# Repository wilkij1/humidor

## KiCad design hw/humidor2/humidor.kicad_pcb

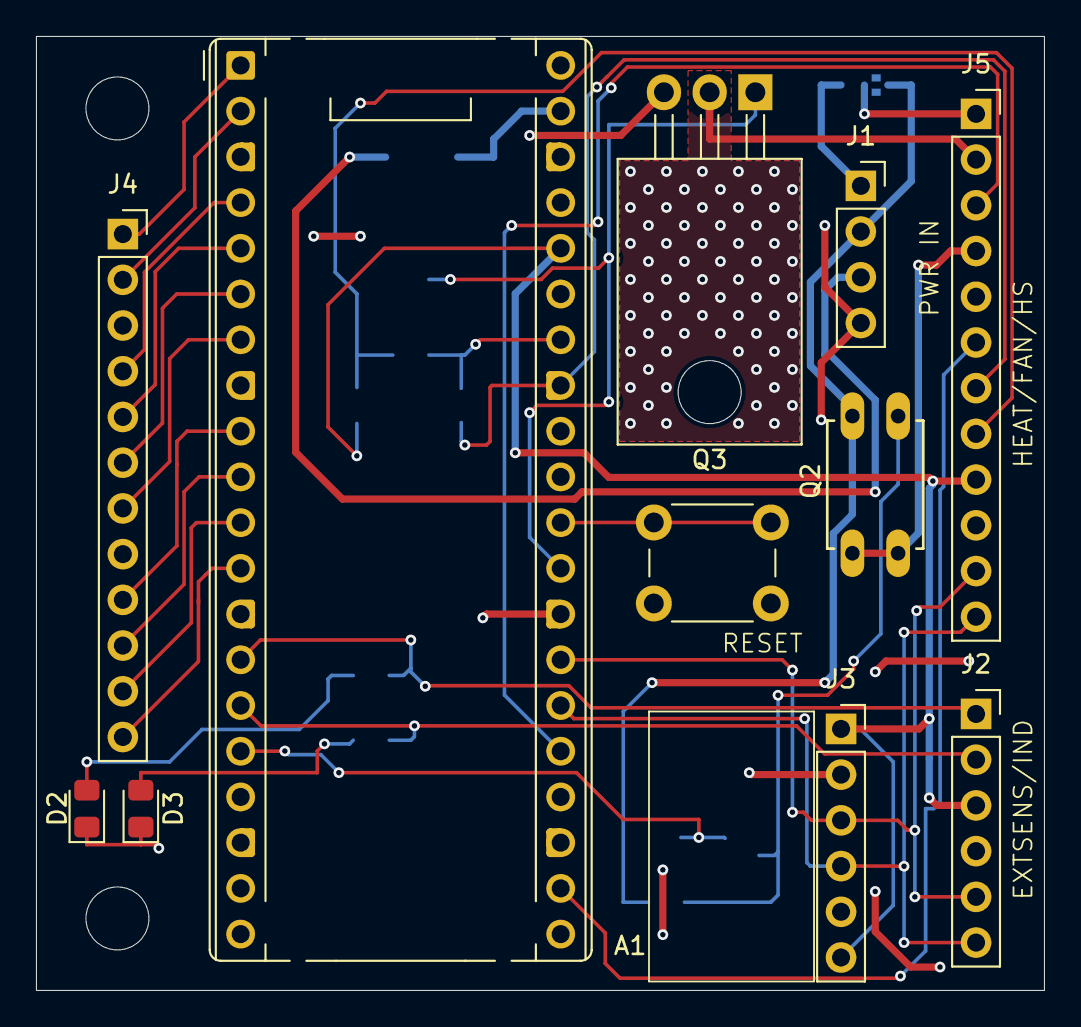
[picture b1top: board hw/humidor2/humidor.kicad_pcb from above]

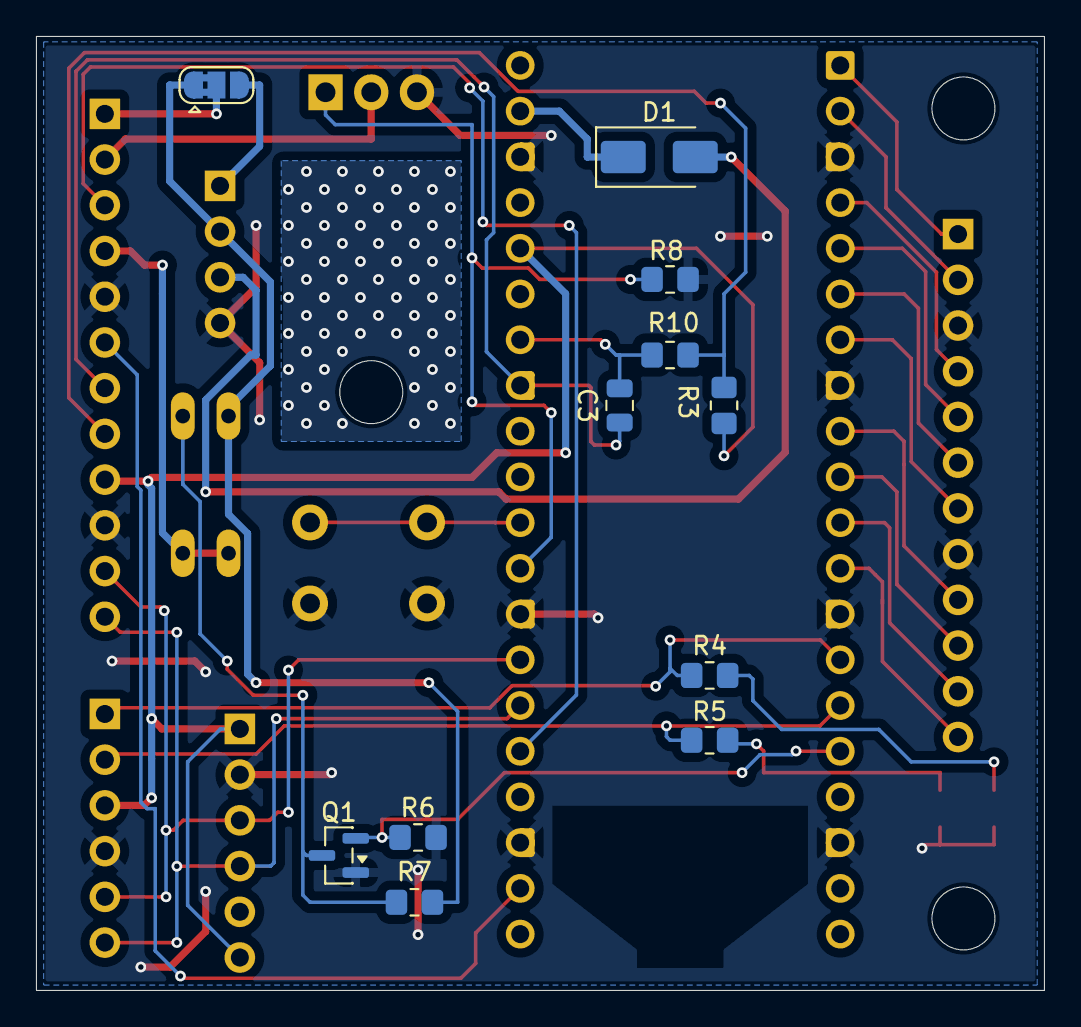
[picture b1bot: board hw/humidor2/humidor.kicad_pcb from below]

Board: 2 copper layers, 56.0 x 53.0 mm, 24 parts (11 on the bottom side), 34 nets.

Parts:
A1: RaspberryPi_Pico_W; RaspberryPi_Pico_Common_THT
C3: 100n; C_0805_2012Metric
D1: 1N5711; D_SMA
D2: RED LED; LED_0805_2012Metric_Pad1.15x1.40mm_HandSolder
D3: GRN LED; LED_0805_2012Metric_Pad1.15x1.40mm_HandSolder
H3, H4: MountingHole; MountingHole_3.5mm
J1: PWR IN; PinSocket_1x04_P2.54mm_Vertical
J2: PWR IN/EXTSENS/IND; PinSocket_1x06_P2.54mm_Vertical
J3: IN_SENSOR; PinSocket_1x06_P2.54mm_Vertical
J4: Conn_01x12; PinSocket_1x12_P2.54mm_Vertical
J5: HEAT/FAN/HS; PinSocket_1x12_P2.54mm_Vertical
JP2: SolderJumper_3_Bridged12; SolderJumper-3_P1.3mm_Bridged2Bar12_RoundedPad1.0x1.5mm
Q1: 2N7002; SOT-23
Q2: IRFD9120; C370-01
Q3: IRF540N; TO-220-3_Horizontal_TabDown
R3: 1k; R_0805_2012Metric_Pad1.20x1.40mm_HandSolder
R4, R5: 330; R_0805_2012Metric_Pad1.20x1.40mm_HandSolder
R6, R7, R8: 100k; R_0805_2012Metric_Pad1.20x1.40mm_HandSolder
R10: 1.6k; R_0805_2012Metric_Pad1.20x1.40mm_HandSolder
SW1: SW_Push; SW_PUSH_6mm_H5mm

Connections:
+3.3V: A1.36 (3V3), J2.3, J3.1, J3.6, J5.9, R3.1
+5V: D1.2 (A), J1.3
+12V: J1.2, JP2.1 (A), Q2.S, R7.1
/AGND: A1.33 (AGND), C3.2, J5.7
/AUX_HEAT: J1.1, JP2.3 (B)
/FAN_EN: A1.16 (GPIO12), Q1.2 (G), R6.1
/FAN_ON: A1.15 (GPIO11), J2.2, R5.1
/FAN_PWM: A1.22 (GPIO17), J5.6
/FAN_PWR: J5.4, Q2.D, Q2.D1
/HEAT_ON: A1.14 (GPIO10), J2.1, R4.1
/HEAT_PWM: A1.29 (GPIO22), Q3.1 (G), R8.1
/HEAT_PWR: J5.1, JP2.2 (C)
/HEAT_SW: J5.2, Q3.2 (D)
/SCL0: A1.27 (GPIO21), J2.5, J3.3, J5.11
/SDA0: A1.26 (GPIO20), J2.6, J3.4, J5.12
/TACH: A1.25 (GPIO19), J5.3
/T_HEATSINK: J5.8, R3.2, R10.2
GND: A1.3 (GND), A1.8 (GND), A1.13 (GND), A1.18 (GND), A1.23 (GND), A1.28 (GND), A1.38 (GND), D2.1 (K), D3.1 (K), J1.4, J2.4, J3.2, J4.3, J4.8, J5.5, J5.10, Q1.1 (S), Q3.3 (S), R6.2, R8.2, SW1.1
unnamed: A1.1 (GPIO0), J4.1
unnamed: A1.2 (GPIO1), J4.2
unnamed: A1.4 (GPIO2), J4.4
unnamed: A1.5 (GPIO3), J4.5
unnamed: A1.6 (GPIO4), J4.6
unnamed: A1.7 (GPIO5), J4.7
unnamed: A1.9 (GPIO6), J4.9
unnamed: A1.10 (GPIO7), J4.10
unnamed: A1.11 (GPIO8), J4.11
unnamed: A1.12 (GPIO9), J4.12
unnamed: A1.34 (GPIO28_ADC2), C3.1, R10.1
unnamed: A1.30 (RUN), SW1.2
unnamed: A1.39 (VSYS), D1.1 (K)
unnamed: D2.2 (A), R4.2
unnamed: D3.2 (A), R5.2
unnamed: Q1.3 (D), Q2.G, R7.2

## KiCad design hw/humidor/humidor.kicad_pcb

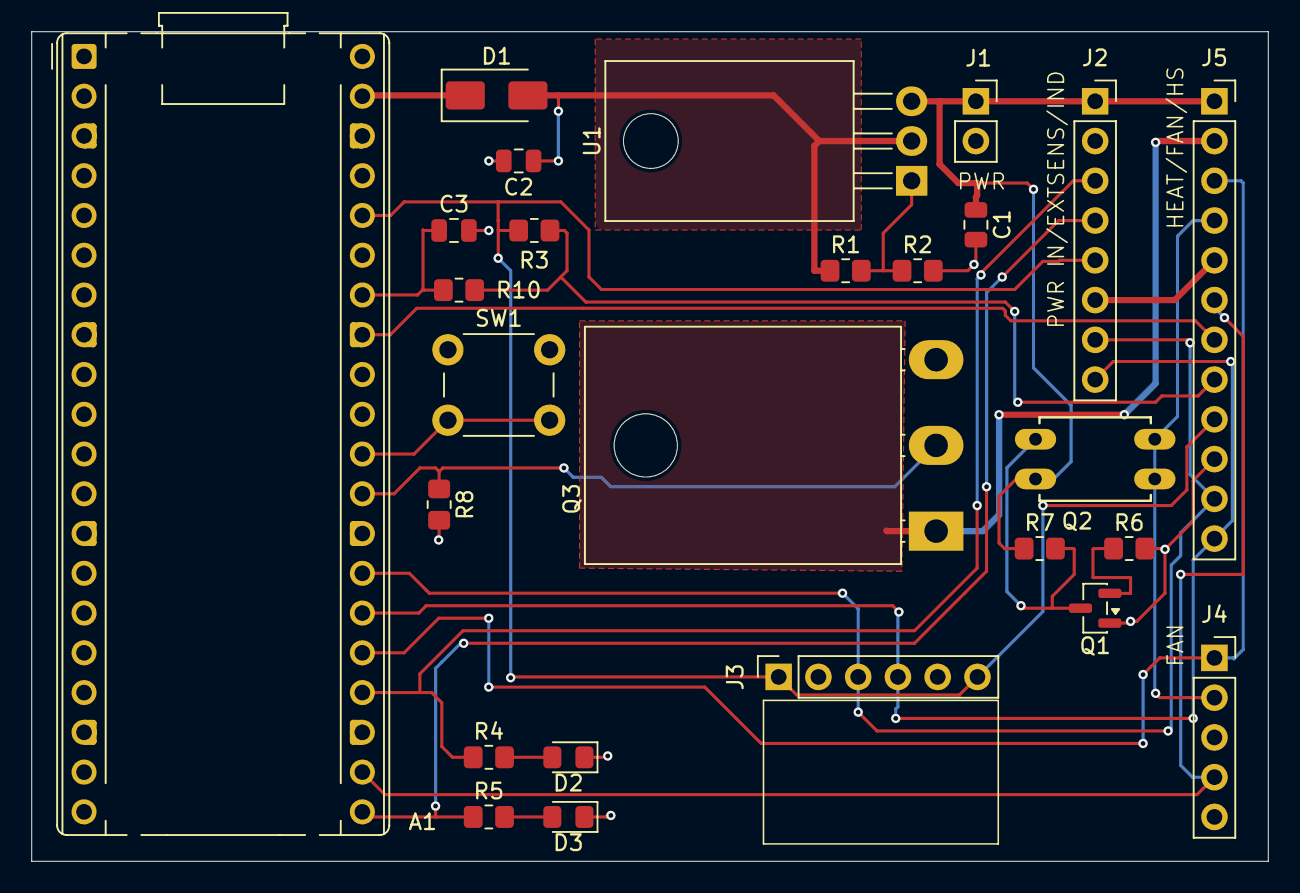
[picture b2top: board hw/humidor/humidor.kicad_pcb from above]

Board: 2 copper layers, 79.0 x 53.0 mm, 26 parts (0 on the bottom side), 23 nets.

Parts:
A1: RaspberryPi_Pico_W; RaspberryPi_Pico_Common_THT
C1, C2: 22u; C_0805_2012Metric
C3: 100n; C_0805_2012Metric
D1: 1N5711; D_SMA
D2: RED LED; LED_0805_2012Metric_Pad1.15x1.40mm_HandSolder
D3: GRN LED; LED_0805_2012Metric_Pad1.15x1.40mm_HandSolder
J1: PWR IN; PinSocket_1x02_P2.54mm_Vertical
J2: PWR IN/EXTSENS/IND; PinSocket_1x08_P2.54mm_Vertical
J3: IN_SENSOR; PinSocket_1x06_P2.54mm_Vertical
J4: Conn_01x05; PinSocket_1x05_P2.54mm_Vertical
J5: HEAT/FAN/HS; PinSocket_1x12_P2.54mm_Vertical
Q1: 2N7002; SOT-23
Q2: IRFD9120; C370-01
Q3: IRL540; TO-218-3_Horizontal_TabDown
R1: 110; R_0805_2012Metric_Pad1.20x1.40mm_HandSolder
R2: 360; R_0805_2012Metric_Pad1.20x1.40mm_HandSolder
R3: 1k; R_0805_2012Metric_Pad1.20x1.40mm_HandSolder
R4, R5: 330; R_0805_2012Metric_Pad1.20x1.40mm_HandSolder
R6, R7, R8: 100k; R_0805_2012Metric_Pad1.20x1.40mm_HandSolder
R10: 1.6k; R_0805_2012Metric_Pad1.20x1.40mm_HandSolder
SW1: SW_Push; SW_PUSH_6mm_H5mm
U1: LT1086-ADJ; TO-220-3_Horizontal_TabDown

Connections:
+3.3V: A1.36 (3V3), J2.5, J3.1, J3.6, J5.9, R3.1
+5V: C2.1, D1.2 (A), R1.1, U1.2 (VO)
+12V: C1.1, J1.1, J2.1, J5.1, Q2.S, R7.1, U1.3 (VI)
/AGND: A1.33 (AGND), J5.7
/FAN_EN: Q1.2 (G), R6.1
/FAN_ON: A1.21 (GPIO16), J2.4, R5.1
/FAN_PWM: A1.22 (GPIO17), J4.4, J5.6
/FAN_PWR: J4.2, J5.4, Q2.D, Q2.D1
/HEAT_ON: A1.24 (GPIO18), J2.3, R4.1
/HEAT_PWM: A1.29 (GPIO22), Q3.2 (G), R8.1
/HEAT_SW: J5.2, Q3.1 (D)
/SCL0: A1.27 (GPIO21), J2.7, J3.3, J5.11
/SDA0: A1.26 (GPIO20), J2.8, J3.4, J5.12
/TACH: A1.25 (GPIO19), J4.1, J5.3
/T_HEATSINK: J5.8, R3.2, R10.2
GND: A1.3 (GND), A1.8 (GND), A1.13 (GND), A1.18 (GND), A1.23 (GND), A1.28 (GND), A1.38 (GND), C1.2, C2.2, C3.2, D2.1 (K), D3.1 (K), J1.2, J2.2, J2.6, J3.2, J4.3, J5.5, J5.10, Q1.1 (S), Q3.3 (S), R2.2, R6.2, R8.2, SW1.1
unnamed: A1.34 (GPIO28_ADC2), C3.1, R10.1
unnamed: A1.30 (RUN), SW1.2
unnamed: A1.39 (VSYS), D1.1 (K)
unnamed: D2.2 (A), R4.2
unnamed: D3.2 (A), R5.2
unnamed: Q1.3 (D), Q2.G, R7.2
unnamed: R1.2, R2.1, U1.1 (ADJ)

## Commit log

2026-02-09 functioning, before change to simple-pid
2026-02-09 basic PID functioning operational and all monitoring functions available
2026-02-09 snapshot before ripping up boot.py
2026-02-09 update prior to establishing remote repository
2026-02-12 prior to refactoring. MQTT basically running
2026-02-18 Modified to get online with home assistant.
2026-02-18 finalized board with all DRC satisfied. Next step is to try double side layout.
2026-02-18 First version of PCB files. Updated .gitignore to skip some Kicad files.
2026-02-19 hw/humidor2/humidor.kicad_pcb
2026-02-19 Version of board sent to OSHPark for fab on 2/19
2026-02-24 functioning version on breadboard, ready for further HA integration
2026-02-24 tweak to status messages
2026-03-05 moving back into shop for more SW development
